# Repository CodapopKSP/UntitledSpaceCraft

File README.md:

# UntitledSpaceCraft

Untitled Space Craft is a modular controller system originally developed by Codapop. For build instructions and information, check the releases for updated documentation.

## License

This project is licensed under the [GNU General Public License v3.0 (GPL-3.0)](https://www.gnu.org/licenses/gpl-3.0.html). 

### Important License Terms

While you are free to use, modify, and redistribute the files in this project under the terms of the GPL-3.0, please note the following restrictions regarding commercial use:

- **Commercial Use**: This project is open source for hobby builders and personal use. However, you **may not** sell the hardware or any products derived from this project without explicit permission from the original creator. 

- **Modification**: You are allowed to modify the files for personal or hobby projects.

- **Attribution**: If you use or adapt this project, please give appropriate credit by mentioning the original creator.

## Contributing

Contributions are welcome! If you'd like to contribute to this project, please fork the repository and submit a pull request.

## Contact

If you have any questions or need further clarification about the license or the project, feel free to contact me at untitledspacecraft.controllers@gmail.com.

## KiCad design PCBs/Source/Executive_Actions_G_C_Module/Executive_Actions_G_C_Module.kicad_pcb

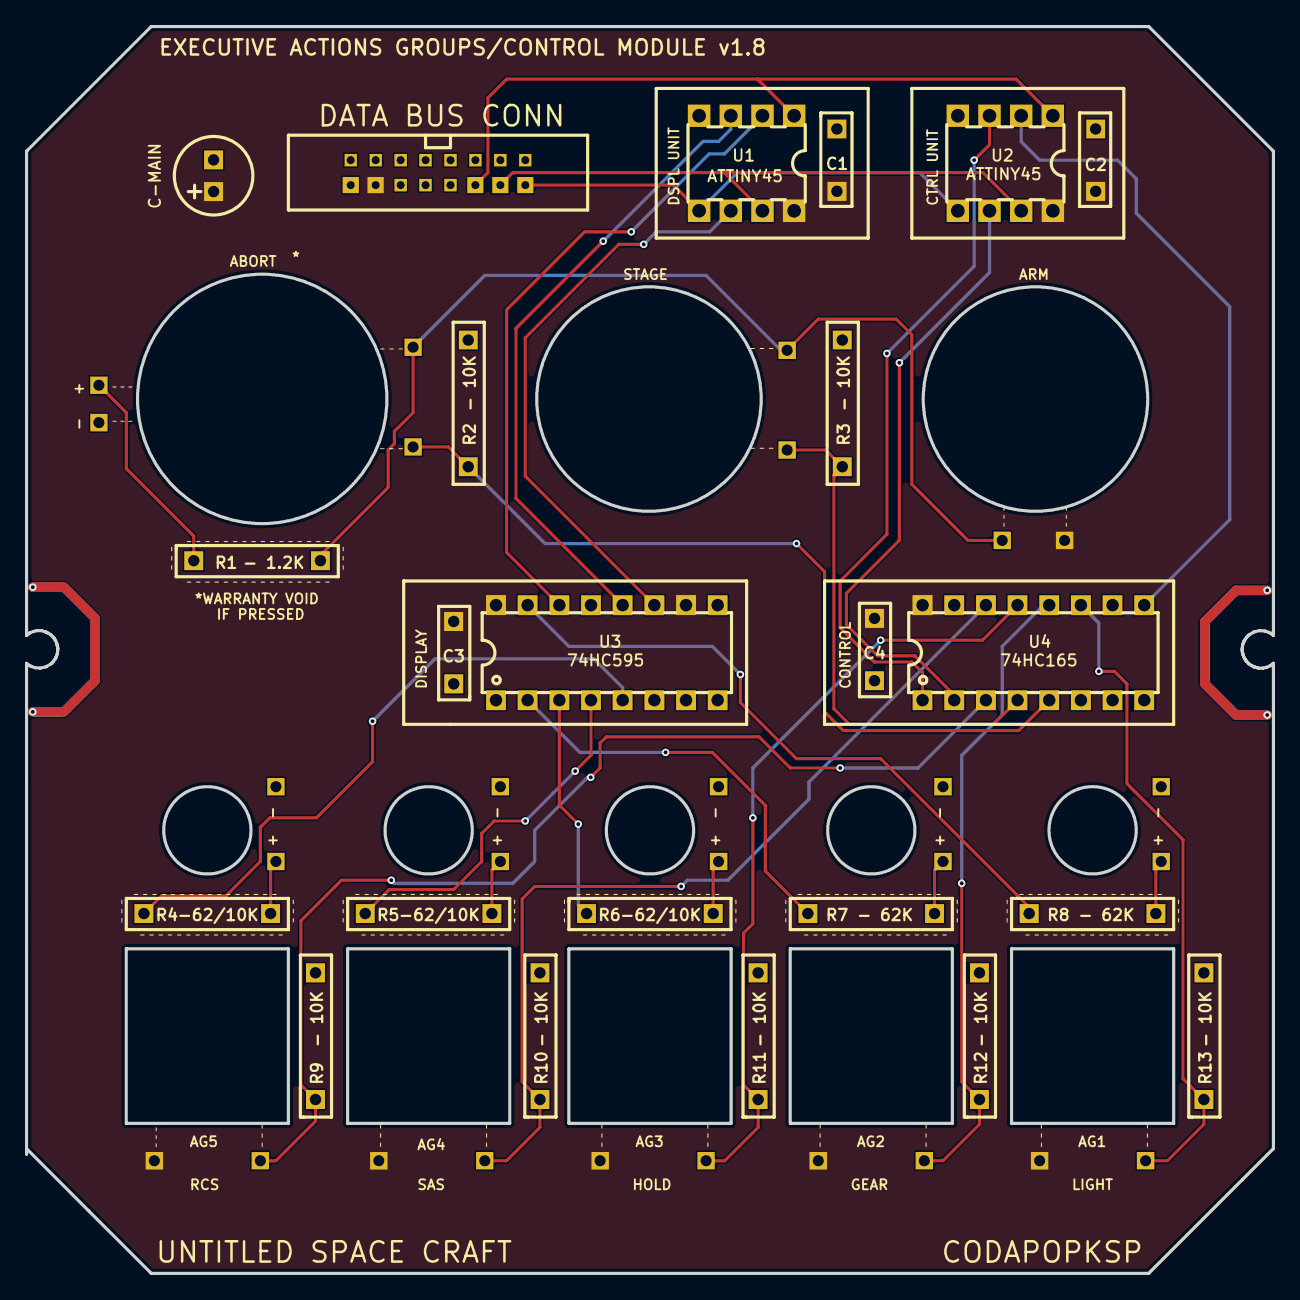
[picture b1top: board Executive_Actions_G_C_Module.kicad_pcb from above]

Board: 2 copper layers, 100.0 x 100.0 mm, 66 parts (0 on the bottom side), 30 nets.

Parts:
C1, C2, C3, C4: C104; TH_CAP_5mm
C-MAIN: 10uf; CAP-D6.3×F2.5
R1: - 1.2K; TH_RES_10mm
R2, R3, R5, R9, R10, R11, R12, R13: - 10K; TH_RES_10mm
R4: -62/10K; TH_RES_10mm
R6: - 62/10K; TH_RES_10mm
R7, R8: - 62K; TH_RES_10mm
TP_+5V: WirePad
TP_ABORT: WirePad
TP_ABORTL: WirePad
TP_ARMED: WirePad
TP_GND: WirePad
TP_STAGE: WirePad
U1, U2: ATtiny45; PDIP-8_L9.3-W6.4-P2.54-LS7.6-BL
U3: 74HC595; DIP-16_L20.0-W6.4-P2.54-LS7.6-BL
U4: 74HC165; DIP-16_L20.0-W6.4-P2.54-LS7.6-BL
WP1, WP2, WP3, WP4, WP5, WP6, WP7, WP8, WP9, WP10, WP11, WP12, WP13, WP14, WP15, WP16, WP47, WP55, WP65, WP75, WP82, WP83, WP84, WP85, WP86, WP87, WP88, WP89, WP90, WP91, WP92, WP93, WP94, WP95, WP96, WP97, WP98, WP99: WPAD-1-30AWG; WPAD-1-PTH-30AWG

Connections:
+5V: C1.2, C2.2, C3.2, C4.2, C-MAIN.1, TP_+5V.1, U1.8, U2.8, U3.10, U3.16, U4.16, WP7.1, WP75.1, WP92.1, WP94.1, WP96.1, WP98.1
ABORT: R2.1, TP_ABORT.1, U4.5
ABORTL: R1.1, TP_ABORTL.1
ARMED: R1.2, TP_ARMED.1, WP82.1, WP83.1
BUTTON1: R13.1, U4.11, WP99.1
BUTTON2: R12.1, U4.12, WP97.1
BUTTON3: R11.1, U4.13, WP95.1
BUTTON4: R10.1, U4.14, WP93.1
BUTTON5: R9.1, U4.3, WP65.1
CLOCK(Y): U2.6, U4.2
CLOCK(Y)2: U1.6, U3.11
DATA(P): U2.2, U4.9
DATA(P)2: U1.2, U3.14
GND: C1.1, C2.1, C3.1, C4.1, C-MAIN.2, R2.2, R3.2, R9.2, R10.2, R11.2, R12.2, R13.2, TP_GND.1, U1.4, U2.4, U3.8, U3.13, U4.6, U4.8, U4.15, WP8.1, WP55.1, WP84.1, WP86.1, WP89.1, WP91.1
LATCH(G): U2.3, U4.1
LATCH(G)2: U1.3, U3.12
LIGHT1: R8.1, U3.15
LIGHT2: R7.1, U3.2
LIGHT3: R6.1, U3.3
LIGHT4: R5.1, U3.4
LIGHT5: R4.1, U3.5
RESET: U1.1, U2.1, WP3.1
SCL: U1.7, U2.7, WP2.1
SDA: U1.5, U2.5, WP1.1
STAGE: R3.1, TP_STAGE.1, U4.4
WP47_1: R8.2, WP87.1
WP47_2: R7.2, WP88.1
WP47_3: R6.2, WP90.1
WP47_4: R5.2, WP85.1
WP47_5: R4.2, WP47.1

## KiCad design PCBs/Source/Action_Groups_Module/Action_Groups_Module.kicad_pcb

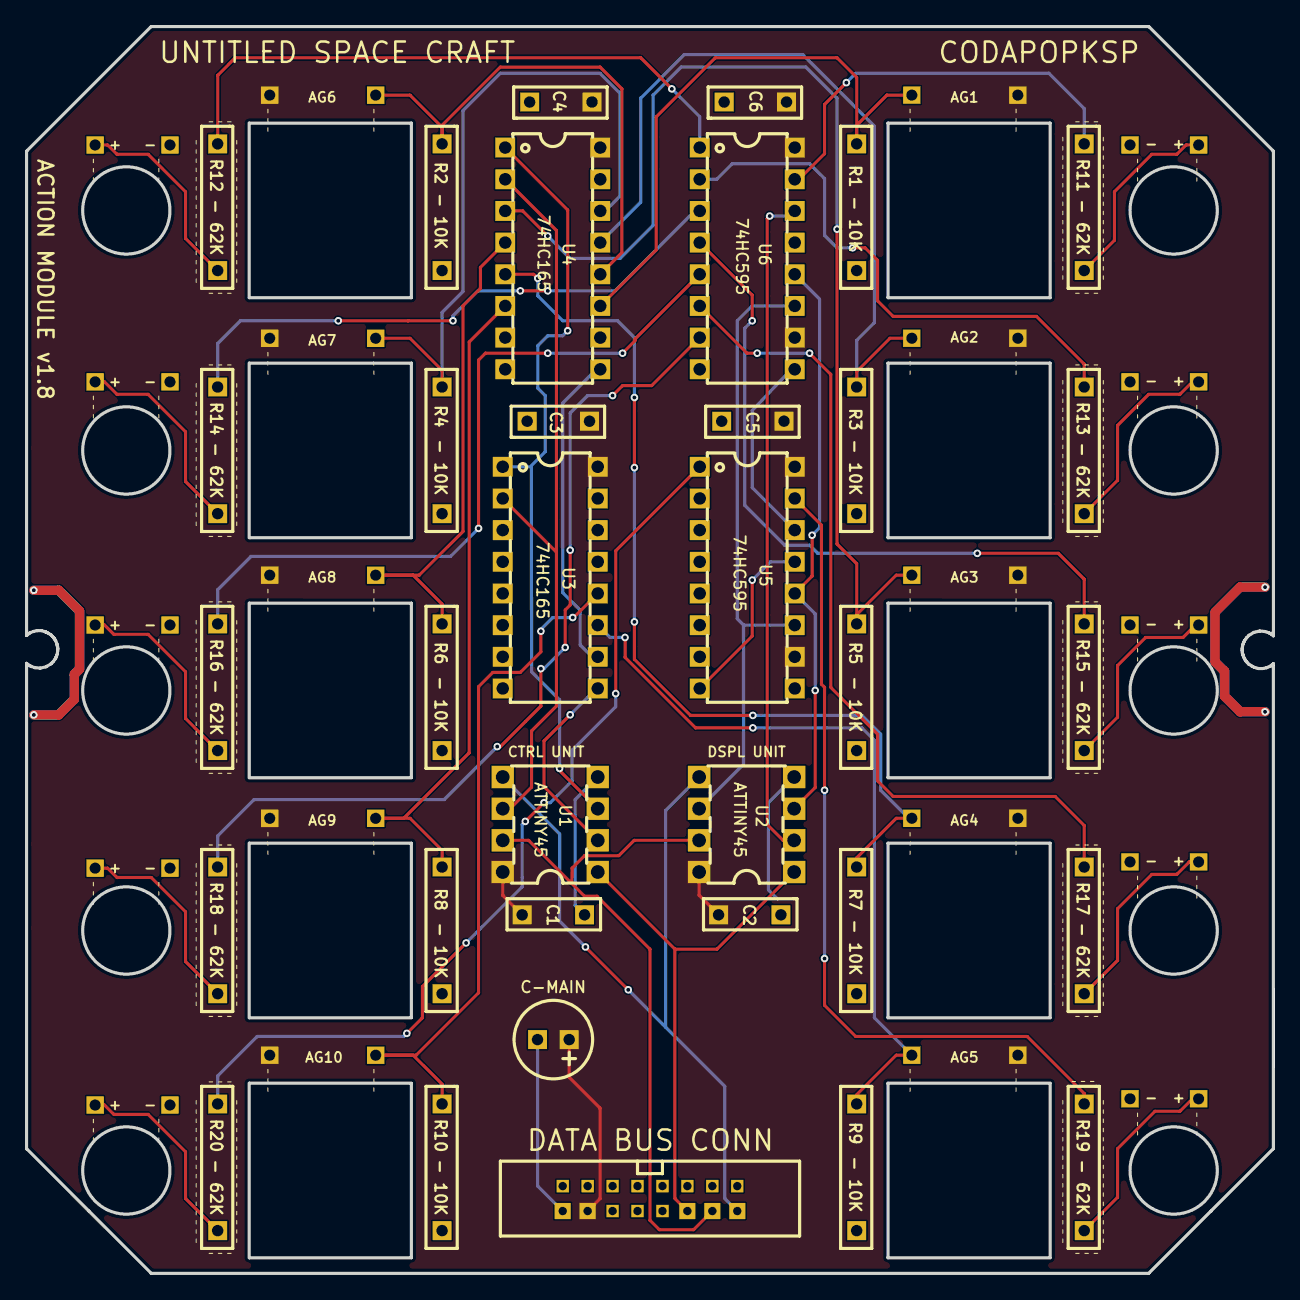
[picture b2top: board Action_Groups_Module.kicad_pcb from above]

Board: 2 copper layers, 100.0 x 100.0 mm, 89 parts (0 on the bottom side), 43 nets.

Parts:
C1, C2, C3, C4, C5, C6: C104; TH_CAP_5mm
C-MAIN: 10uf; CAP-D6.3×F2.5
R1, R2, R3, R4, R5, R6, R7, R8, R9, R10: - 10K; TH_RES_10mm
R11, R12, R13, R14, R15, R16, R17, R18, R19, R20: - 62K; TH_RES_10mm
U1, U2: ATtiny45; PDIP-8_L9.3-W6.4-P2.54-LS7.6-BL
U3, U4: 74HC165; DIP-16_L20.0-W6.4-P2.54-LS7.6-BL
U5, U6: 74HC595; DIP-16_L20.0-W6.4-P2.54-LS7.6-BL
WP41, WP42, WP43, WP44, WP45, WP46, WP47, WP48, WP49, WP50, WP51, WP52, WP53, WP54, WP55, WP56, WP57, WP58, WP59, WP60, WP61, WP62, WP63, WP64, WP65, WP66, WP67, WP68, WP69, WP70, WP71, WP72, WP73, WP74, WP75, WP76, WP77, WP78, WP83, WP84, WP85, WP86, WP87, WP88, WP89, WP90, WP91, WP92, WP93, WP94, WP95, WP96, WP97, WP98, WP99, WP100: WPAD-1-30AWG; WPAD-1-PTH-30AWG

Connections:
+5V: C1.2, C2.2, C3.2, C4.2, C5.2, C6.2, C-MAIN.1, U1.8, U2.8, U3.16, U4.16, U5.10, U5.16, U6.10, U6.16, WP71.1, WP72.1, WP73.1, WP74.1, WP75.1, WP76.1, WP77.1, WP78.1, WP83.1, WP84.1, WP92.1
CLOCK(Y): U1.6, U3.2, U4.2
CLOCK(Y)2: U2.6, U5.11, U6.11
DATA(B): U3.10, U4.9
DATA(B)2: U5.14, U6.9
DATA(P): U1.2, U3.9
DATA(P)2: U2.2, U6.14
GND: C1.1, C2.1, C3.1, C4.1, C5.1, C6.1, C-MAIN.2, R1.2, R2.2, R3.2, R4.2, R5.2, R6.2, R7.2, R8.2, R9.2, R10.2, U1.4, U2.4, U3.3, U3.4, U3.5, U3.6, U3.8, U3.13, U3.14, U3.15, U4.8, U4.15, U5.8, U5.13, U6.8, U6.13, WP49.1, WP50.1, WP51.1, WP52.1, WP53.1, WP54.1, WP55.1, WP56.1, WP57.1, WP59.1, WP91.1
LATCH(G): U1.3, U3.1, U4.1
LATCH(G)2: U2.3, U5.12, U6.12
LIGHT1: R11.1, U6.15
LIGHT2: R12.1, U6.1
LIGHT3: R13.1, U6.2
LIGHT4: R14.1, U6.3
LIGHT5: R15.1, U6.4
LIGHT6: R16.1, U6.5
LIGHT7: R17.1, U6.6
LIGHT8: R18.1, U6.7
LIGHT9: R19.1, U5.15
LIGHT10: R20.1, U5.1
RESET: U1.1, U2.1, WP96.1
SAS1: R1.1, U4.11, WP61.1
SAS2: R2.1, U4.12, WP62.1
SAS3: R3.1, U4.13, WP63.1
SAS4: R4.1, U4.14, WP64.1
SAS5: R5.1, U4.3, WP65.1
SAS6: R6.1, U4.4, WP66.1
SAS7: R7.1, U4.5, WP67.1
SAS8: R8.1, U4.6, WP68.1
SAS9: R9.1, U3.11, WP69.1
SAS10: R10.1, U3.12, WP70.1
SCL: U1.7, U2.7, WP97.1
SDA: U1.5, U2.5, WP98.1
WP41_1: R18.2, WP41.1
WP42_1: R17.2, WP42.1
WP43_1: R16.2, WP43.1
WP44_1: R15.2, WP44.1
WP45_1: R14.2, WP45.1
WP46_1: R13.2, WP46.1
WP47_1: R12.2, WP47.1
WP48_1: R11.2, WP48.1
WP58_1: R19.2, WP58.1
WP60_1: R20.2, WP60.1

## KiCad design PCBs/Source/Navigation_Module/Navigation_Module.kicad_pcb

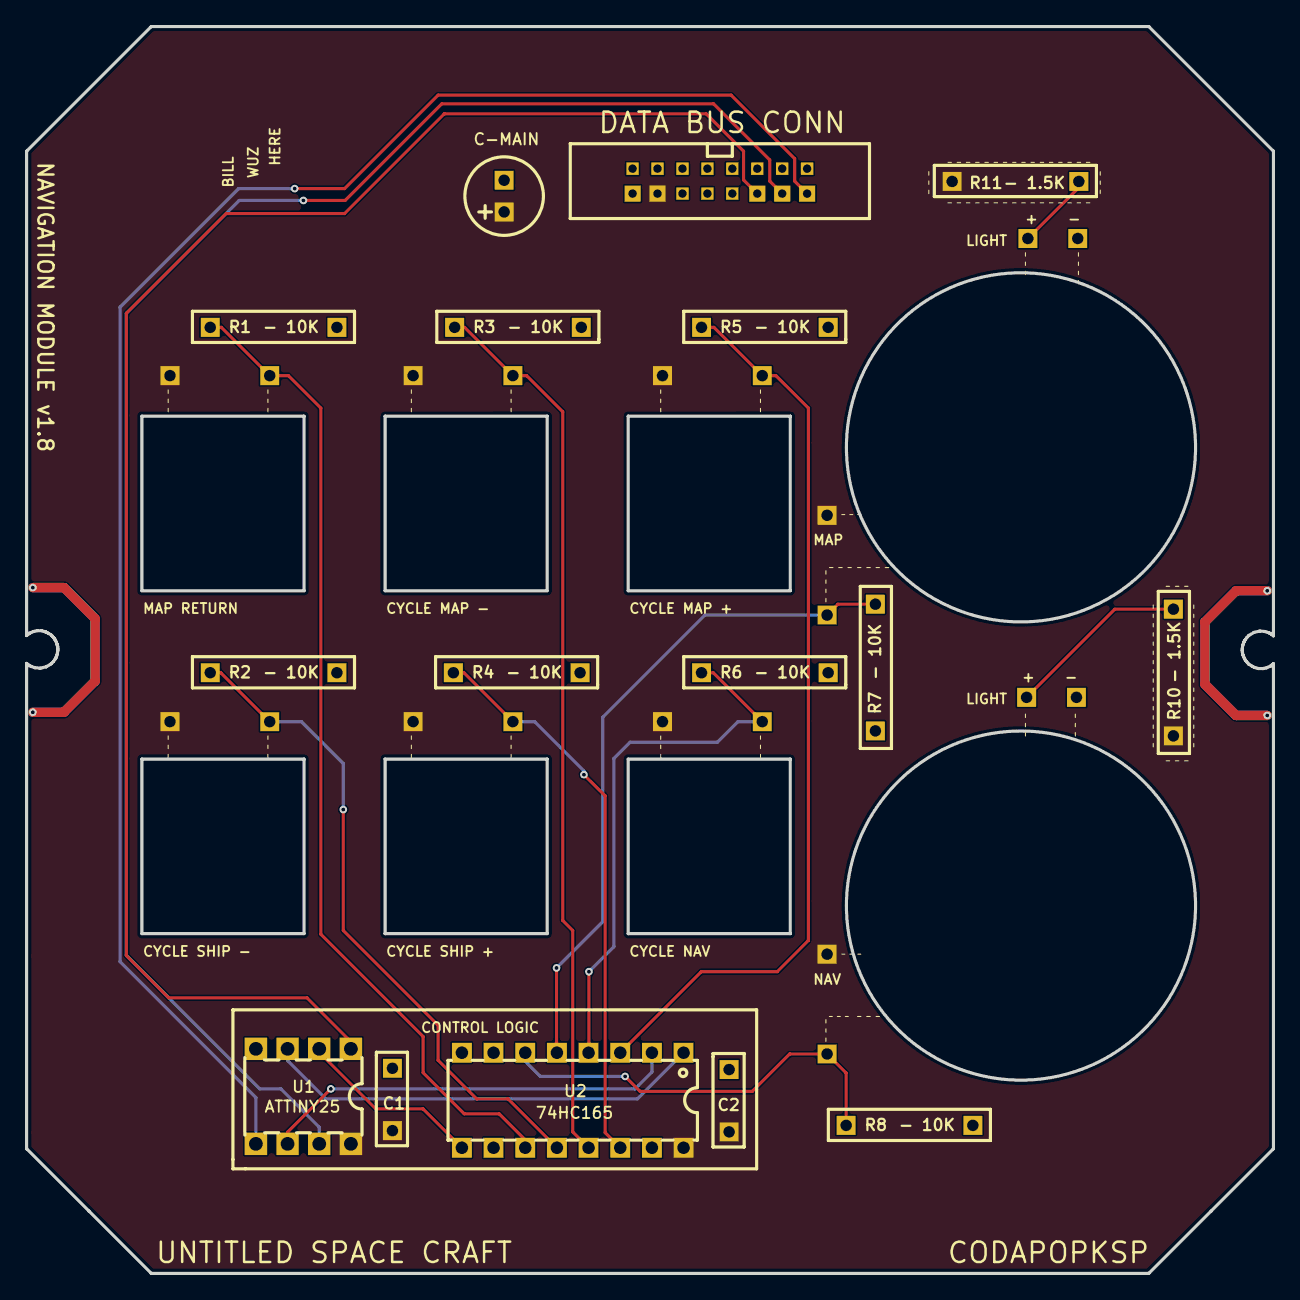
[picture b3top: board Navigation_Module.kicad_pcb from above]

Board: 2 copper layers, 100.0 x 100.0 mm, 51 parts (0 on the bottom side), 16 nets.

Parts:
C1, C2: C104; TH_CAP_5mm
C-MAIN: 10uf; CAP-D6.3×F2.5
R1, R2, R3, R4, R5, R6, R7, R8: - 10K; TH_RES_10mm
R10, R11: - 1.5K; TH_RES_10mm
TP_+5V, TP_+5V#2, TP_+5V#3, TP_+5V#4, TP_+5V#5, TP_+5V#6, TP_+5V#7, TP_+5V#8: WirePad
TP_GND: WirePad
TP_GND#2: WirePad
TP_LIGHT1, TP_LIGHT2: WirePad
TP_N1, TP_N2, TP_N3, TP_N4, TP_N5, TP_N6, TP_N7, TP_N8: WirePad
U1: ATtiny25; PDIP-8_L9.3-W6.4-P2.54-LS7.6-BL
U2: 74HC165; DIP-16_L20.0-W6.4-P2.54-LS7.6-BL
WP17, WP18, WP19, WP20, WP21, WP22, WP23, WP24, WP25, WP26, WP27, WP28, WP29, WP30, WP31, WP32: WPAD-1-30AWG; WPAD-1-PTH-30AWG

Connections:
+5V: C1.2, C2.2, C-MAIN.1, R10.1, R11.2, U1.8, U2.16, WP25.1
CLOCK(Y): U1.6, U2.2
DATA(P): U1.2, U2.9
GND: C1.1, C2.1, C-MAIN.2, R1.1, R2.1, R3.1, R4.1, R5.1, R6.1, R7.1, R8.1, U1.4, U2.8, U2.15, WP26.1
LATCH(G): U1.3, U2.1
N1: R1.2, U2.11
N2: R2.2, U2.12
N3: R3.2, U2.13
N4: R4.2, U2.14
N5: R5.2, U2.3
N6: R6.2, U2.4
N7: R7.2, U2.5
N8: R8.2, U2.6
RESET: U1.1, WP21.1
SCL: U1.7, WP20.1
SDA: U1.5, WP19.1

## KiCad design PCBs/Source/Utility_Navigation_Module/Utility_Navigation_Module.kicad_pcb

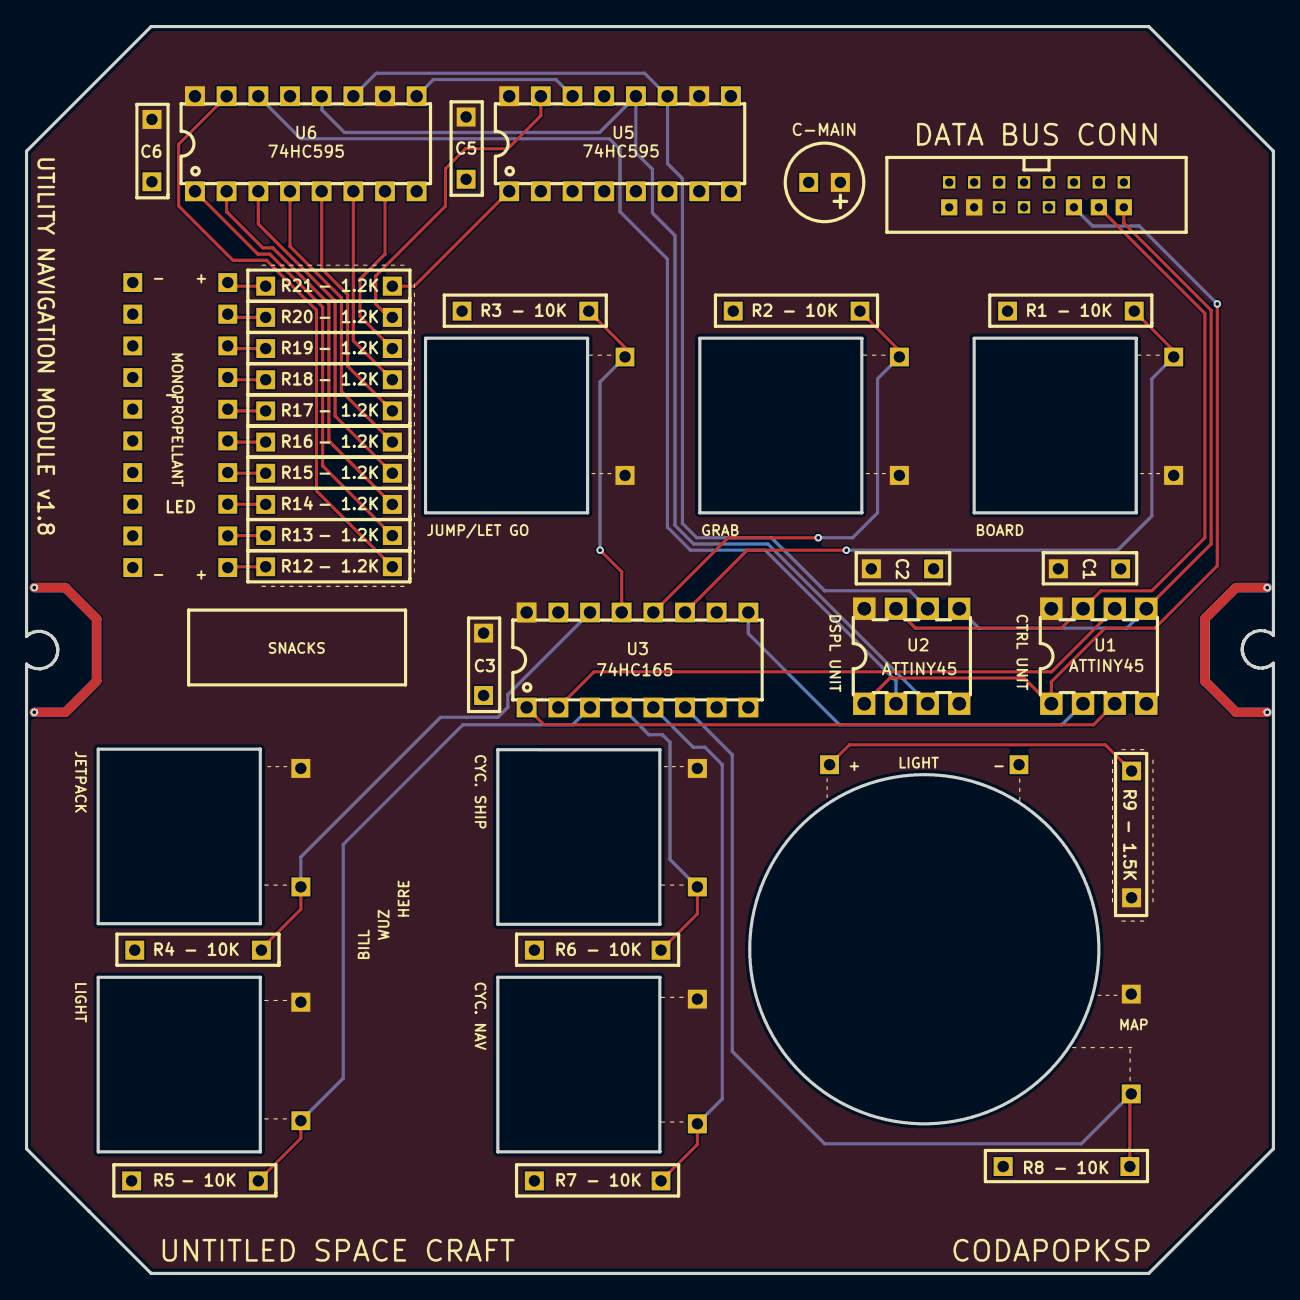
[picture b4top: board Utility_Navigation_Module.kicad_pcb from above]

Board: 2 copper layers, 100.0 x 100.0 mm, 65 parts (0 on the bottom side), 40 nets.

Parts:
C1, C2, C3, C5, C6: C104; TH_CAP_5mm
C-MAIN: 10uf; CAP-D6.3×F2.5
LED: _
R1, R2, R3, R4, R5, R6, R7, R8: - 10K; TH_RES_10mm
R9: - 1.5K; TH_RES_10mm
R12, R13, R14, R15, R16, R17, R18, R19, R20, R21: - 1.2K; TH_RES_10mm
TP_+5V, TP_+5V#2, TP_+5V#3, TP_+5V#4, TP_+5V#5, TP_+5V#6, TP_+5V#7, TP_+5V#8: WirePad
TP_EVA1, TP_EVA2, TP_EVA3, TP_EVA4, TP_EVA5: WirePad
TP_GND: WirePad
TP_LIGHT0: WirePad
TP_N1, TP_N2, TP_N3: WirePad
U1, U2: ATtiny45; PDIP-8_L9.3-W6.4-P2.54-LS7.6-BL
U3: 74HC165; DIP-16_L20.0-W6.4-P2.54-LS7.6-BL
U5, U6: 74HC595; DIP-16_L20.0-W6.4-P2.54-LS7.6-BL
WP1, WP2, WP3, WP4, WP5, WP6, WP7, WP8, WP9, WP10, WP11, WP12, WP13, WP14, WP15, WP16: WPAD-1-30AWG; WPAD-1-PTH-30AWG

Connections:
+5V: C1.2, C2.2, C3.2, C5.2, C6.2, C-MAIN.1, R9.2, TP_+5V.8, TP_+5V#4.8, TP_+5V#6.9, TP_+5V#8.15, U1.8, U2.8, U3.16, U5.10, U5.16, U6.10, U6.16, WP7.1
CLOCK(Y): U1.6, U3.2
CLOCK(Y)2: U2.6, U5.11, U6.11
DATA(B)2: U5.14, U6.9
DATA(P): U1.2, U3.9
DATA(P)2: U2.2, U6.14
EVA1: R1.1, TP_EVA1.20, U3.11
EVA2: R2.1, TP_EVA2.18, U3.12
EVA3: R3.1, TP_EVA3.16, U3.13
EVA4: R4.1, TP_EVA4.1, U3.14
EVA5: R5.1, TP_EVA5.1, U3.3
GND: C1.1, C2.1, C3.1, C5.1, C6.1, C-MAIN.2, LED.GND, R1.2, R2.2, R3.2, R4.2, R5.2, R6.2, R7.2, R8.2, U1.4, U2.4, U3.8, U3.15, U5.8, U5.13, U6.8, U6.13, WP8.1
LATCH(G): U1.3, U3.1
LATCH(G)2: U2.3, U5.12, U6.12
LIGHT1: R12.1, U6.15
LIGHT2: R13.1, U6.1
LIGHT3: R14.1, U6.2
LIGHT4: R15.1, U6.3
LIGHT5: R16.1, U6.4
LIGHT6: R17.1, U6.5
LIGHT7: R18.1, U6.6
LIGHT8: R19.1, U6.7
LIGHT9: R20.1, U5.15
LIGHT10: R21.1, U5.1
N1: R6.1, TP_N1.2, U3.4
N2: R7.1, U3.5
N3: R8.1, U3.6
RESET: U1.1, U2.1, WP3.1
SCL: U1.7, U2.7, WP2.1
SDA: U1.5, U2.5, WP1.1
WP41_1: LED.GND, R19.2
WP42_1: LED.GND, R18.2
WP43_1: LED.GND, R17.2
WP44_1: LED.GND, R16.2
WP45_1: LED.GND, R15.2
WP46_1: LED.GND, R14.2
WP47_1: LED.GND, R13.2
WP48_1: LED.GND, R12.2
WP58_1: LED.GND, R20.2
WP60_1: LED.GND, R21.2

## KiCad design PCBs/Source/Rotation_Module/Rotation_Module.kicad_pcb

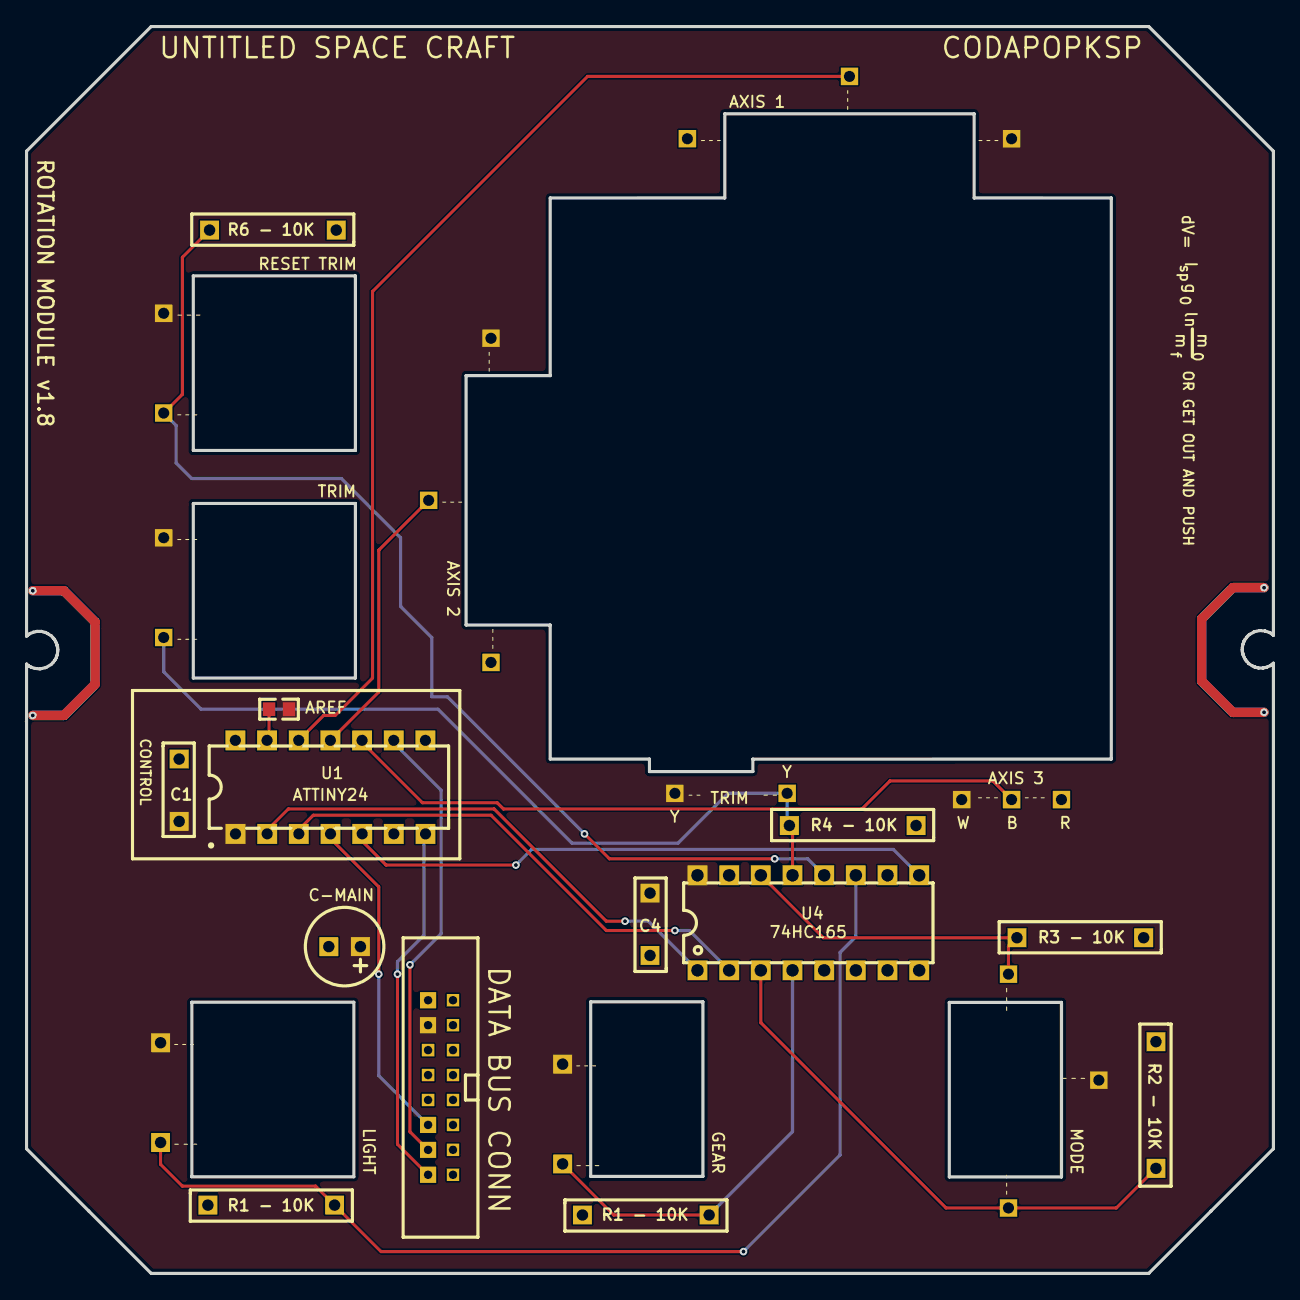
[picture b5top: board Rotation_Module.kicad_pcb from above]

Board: 2 copper layers, 100.0 x 100.0 mm, 63 parts (0 on the bottom side), 18 nets.

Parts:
AREF: 10k; R0603
C1, C4: C104; TH_CAP_5mm
C-MAIN: 10uf; CAP-D6.3×F2.5
R1, R1#2, R2, R3, R4, R6: - 10K; TH_RES_10mm
TP_+5V, TP_+5V#2, TP_+5V#3, TP_+5V#4, TP_+5V#5, TP_+5V#6, TP_+5V#7, TP_+5V#8, TP_+5V#9, TP_+5V#10: WirePad
TP_AREF: WirePad
TP_AXIS1, TP_AXIS1#2, TP_AXIS2, TP_AXIS2#2, TP_AXIS3, TP_AXIS3#2: WirePad
TP_CLOCK_Y_: WirePad
TP_CRUISE: WirePad
TP_DATA_P_: WirePad
TP_GEAR: WirePad
TP_GND: WirePad
TP_GND#2, TP_GND#3, TP_GND#4: WirePad
TP_LATCH_G_: WirePad
TP_LIGHTS: WirePad
TP_MODE1, TP_MODE2: WirePad
TP_Pad_gge45412: WirePad
TP_RESET: WirePad
TP_RESETTRIM: WirePad
TP_SCL: WirePad
TP_SDA: WirePad
TP_TRIM: WirePad
TP_TRIM#2: WirePad
U4: 74HC165; DIP-16_L20.0-W6.4-P2.54-LS7.6-BL
WP11, WP24, WP25, WP38, WP39, WP43, WP44, WP45, WP46, WP47, WP48, WP49, WP50, WP51, WP52, WP53: WPAD-1-30AWG; WPAD-1-PTH-30AWG

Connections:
+5V: AREF.2, C1.2, C4.2, C-MAIN.1, TP_+5V.1, TP_+5V#2.1, TP_+5V#3.1, TP_+5V#4.1, TP_+5V#5.1, TP_+5V#6.1, TP_+5V#7.1, TP_+5V#8.1, TP_+5V#9.1, TP_+5V#10.1, U4.16, WP46.1
AREF: AREF.1, TP_AREF.13
AXIS1: TP_AXIS1.12, TP_AXIS1#2.1
AXIS2: TP_AXIS2.11, TP_AXIS2#2.1
AXIS3: TP_AXIS3.10, TP_AXIS3#2.1
CLOCK(Y): TP_CLOCK_Y_.3, U4.2
DATA(P): TP_DATA_P_.5, U4.9
GEAR: R1#2.2, TP_GEAR.1, U4.4
GND: C1.1, C4.1, C-MAIN.2, R1.1, R1#2.1, R2.1, R3.1, R4.1, R6.1, TP_GND.1, TP_GND#2.1, TP_GND#3.14, TP_GND#4.1, U4.5, U4.6, U4.8, U4.15, WP45.1
LATCH(G): TP_LATCH_G_.2, U4.1
LIGHTS: R1.2, TP_LIGHTS.1, U4.11
MODE1: R3.2, TP_MODE1.1, U4.14
MODE2: R2.2, TP_MODE2.1, U4.3
RESET: TP_RESET.4, WP50.1
RESETTRIM: R6.2, TP_RESETTRIM.1, U4.12
SCL: TP_SCL.9, WP51.1
SDA: TP_SDA.7, WP52.1
TRIM: R4.2, TP_TRIM.1, TP_TRIM#2.1, U4.13

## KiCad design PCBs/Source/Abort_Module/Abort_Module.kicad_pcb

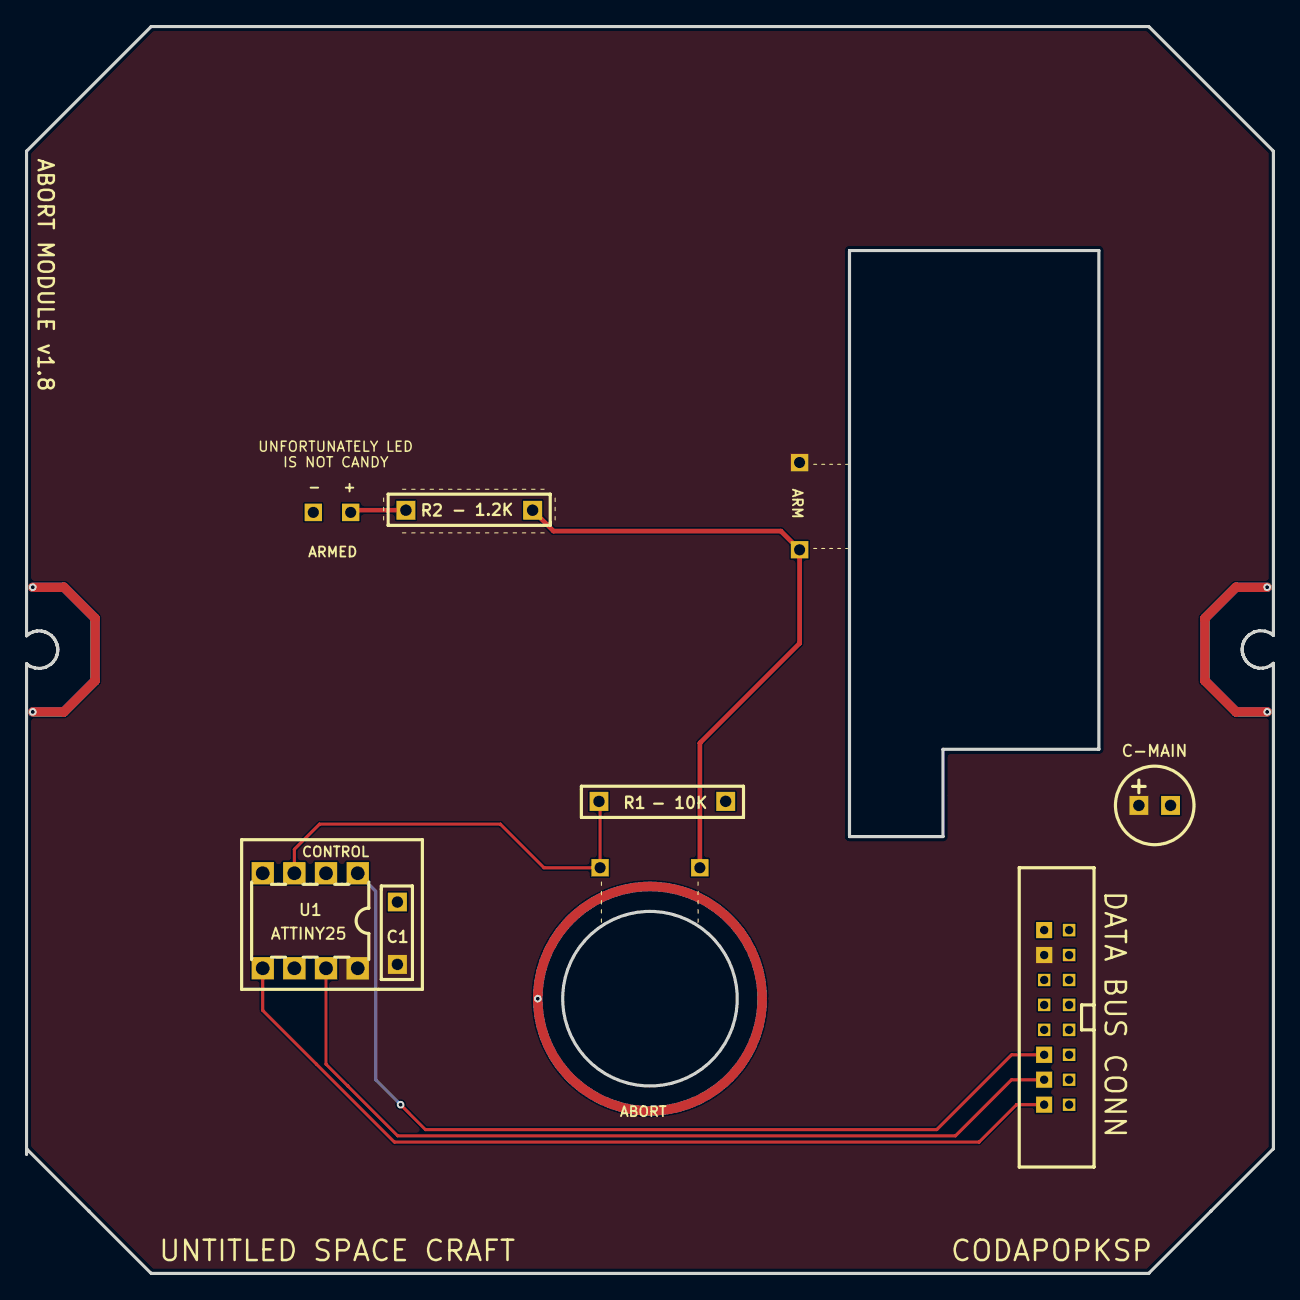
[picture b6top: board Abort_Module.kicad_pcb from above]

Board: 2 copper layers, 100.0 x 100.0 mm, 27 parts (0 on the bottom side), 8 nets.

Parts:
C1: C104; TH_CAP_5mm
C-MAIN: 1u; CAP-D6.3×F2.5
R1: - 10K; TH_RES_10mm
R2: - 1.2K; TH_RES_10mm
TP_+5V: WirePad
TP_ARMED: WirePad
TP_GND: WirePad
TP_LIGHT: WirePad
TP_STAGE: WirePad
U1: ATtiny25; PDIP-8_L9.3-W6.4-P2.54-LS7.6-BL
WP84, WP85, WP86, WP87, WP88, WP89, WP90, WP91, WP92, WP93, WP94, WP95, WP96, WP97, WP98, WP99, WP100: WPAD-1-30AWG; WPAD-1-PTH-30AWG

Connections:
+5V: C1.2, C-MAIN.1, TP_+5V.1, U1.8, WP92.1
ARMED: R2.1, TP_ARMED.1, WP100.1
GND: C1.1, C-MAIN.2, R1.2, TP_GND.1, U1.4, WP93.1
LIGHT: R2.2, TP_LIGHT.1
RESET: U1.1, WP88.1
SCL: U1.7, WP87.1
SDA: U1.5, WP86.1
STAGE: R1.1, TP_STAGE.1, U1.3

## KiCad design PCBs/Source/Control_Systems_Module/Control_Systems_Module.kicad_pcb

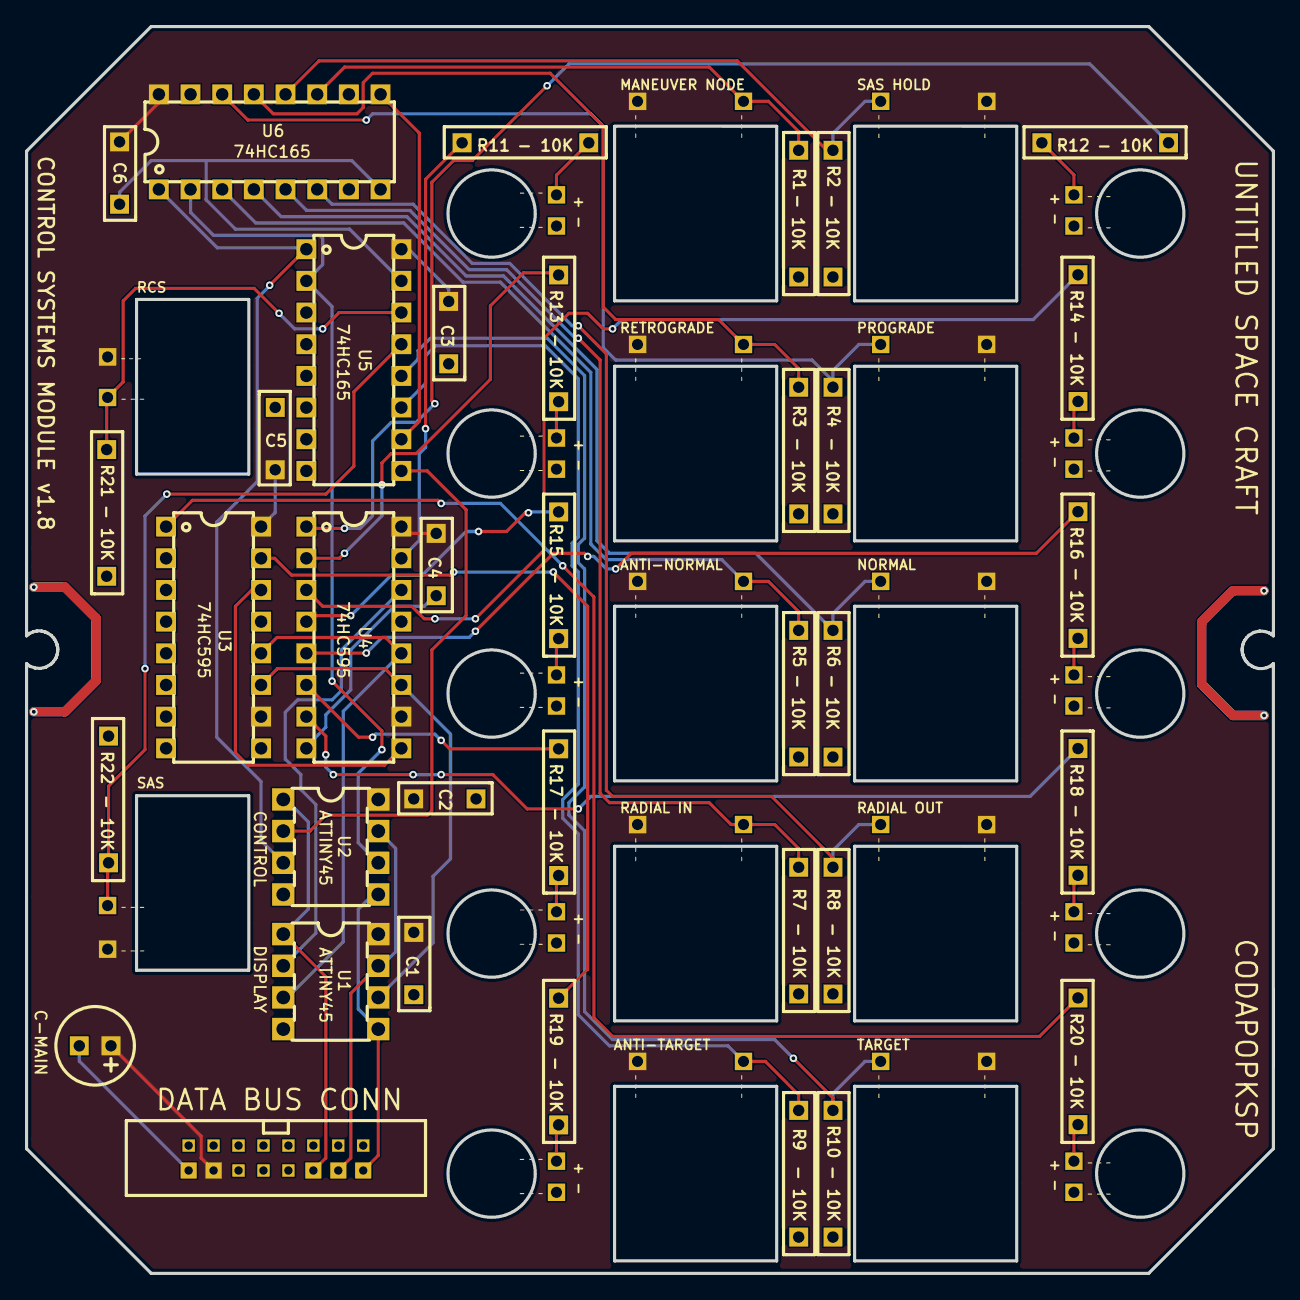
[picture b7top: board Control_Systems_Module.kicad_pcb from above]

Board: 2 copper layers, 100.0 x 100.0 mm, 95 parts (0 on the bottom side), 45 nets.

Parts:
C1, C2, C3, C4, C5, C6: C104; TH_CAP_5mm
C-MAIN: 10uf; CAP-D6.3×F2.5
R1, R2, R3, R4, R5, R6, R7, R8, R9, R10, R11, R12, R13, R14, R15, R16, R17, R18, R19, R20, R21, R22: - 10K; TH_RES_10mm
U1, U2: ATtiny45; PDIP-8_L9.3-W6.4-P2.54-LS7.6-BL
U3, U4: 74HC595; DIP-16_L20.0-W6.4-P2.54-LS7.6-BL
U5, U6: 74HC165; DIP-16_L20.0-W6.4-P2.54-LS7.6-BL
WP1, WP2, WP3, WP4, WP5, WP6, WP7, WP8, WP9, WP10, WP11, WP12, WP13, WP14, WP15, WP16, WP41, WP42, WP43, WP44, WP45, WP46, WP47, WP48, WP49, WP50, WP51, WP52, WP53, WP54, WP55, WP56, WP57, WP58, WP59, WP60, WP61, WP62, WP63, WP64, WP65, WP66, WP67, WP68, WP69, WP70, WP71, WP72, WP73, WP74, WP75, WP76, WP77, WP78, WP79, WP80, WP81, WP82, WP83, WP84: WPAD-1-30AWG; WPAD-1-PTH-30AWG

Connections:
+5V: C1.2, C2.2, C3.2, C4.2, C5.2, C6.2, C-MAIN.1, U1.8, U2.8, U3.10, U3.16, U4.10, U4.16, U5.16, U6.16, WP7.1, WP71.1, WP72.1, WP73.1, WP74.1, WP75.1, WP76.1, WP77.1, WP78.1, WP81.1, WP82.1, WP83.1, WP84.1
CLOCK(Y): U2.6, U5.2, U6.2
CLOCK(Y)2: U1.6, U3.11, U4.11
DATA(B): U5.10, U6.9
DATA(B)2: U3.14, U4.9
DATA(P): U2.2, U5.9
DATA(P)2: U1.2, U4.14
GND: C1.1, C2.1, C3.1, C4.1, C5.1, C6.1, C-MAIN.2, R1.1, R2.1, R3.1, R4.1, R5.1, R6.1, R7.1, R8.1, R9.1, R10.1, R21.1, R22.1, U1.4, U2.4, U3.8, U3.13, U4.8, U4.13, U5.3, U5.4, U5.5, U5.6, U5.8, U5.15, U6.8, U6.15, WP8.1, WP49.1, WP50.1, WP51.1, WP52.1, WP53.1, WP54.1, WP55.1, WP56.1, WP57.1, WP59.1
LATCH(G): U2.3, U5.1, U6.1
LATCH(G)2: U1.3, U3.12, U4.12
LIGHT1: R11.2, U4.15
LIGHT2: R12.1, U4.1
LIGHT3: R13.2, U4.2
LIGHT4: R14.1, U4.3
LIGHT5: R15.2, U4.4
LIGHT6: R16.1, U4.5
LIGHT7: R17.2, U4.6
LIGHT8: R18.1, U4.7
LIGHT9: R19.2, U3.15
LIGHT10: R20.1, U3.1
RCS: R21.2, U5.14, WP80.1
RESET: U1.1, U2.1, WP3.1
SAS: R22.2, U5.13, WP79.1
SAS1: R1.2, U6.11, WP61.1
SAS2: R2.2, U6.12, WP62.1
SAS3: R3.2, U6.13, WP63.1
SAS4: R4.2, U6.14, WP64.1
SAS5: R5.2, U6.3, WP65.1
SAS6: R6.2, U6.4, WP66.1
SAS7: R7.2, U6.5, WP67.1
SAS8: R8.2, U6.6, WP68.1
SAS9: R9.2, U5.11, WP69.1
SAS10: R10.2, U5.12, WP70.1
SCL: U1.7, U2.7, WP2.1
SDA: U1.5, U2.5, WP1.1
WP41_1: R18.2, WP41.1
WP42_1: R17.1, WP42.1
WP43_1: R16.2, WP43.1
WP44_1: R15.1, WP44.1
WP45_1: R14.2, WP45.1
WP46_1: R13.1, WP46.1
WP47_1: R12.2, WP47.1
WP48_1: R11.1, WP48.1
WP58_1: R19.1, WP58.1
WP60_1: R20.2, WP60.1

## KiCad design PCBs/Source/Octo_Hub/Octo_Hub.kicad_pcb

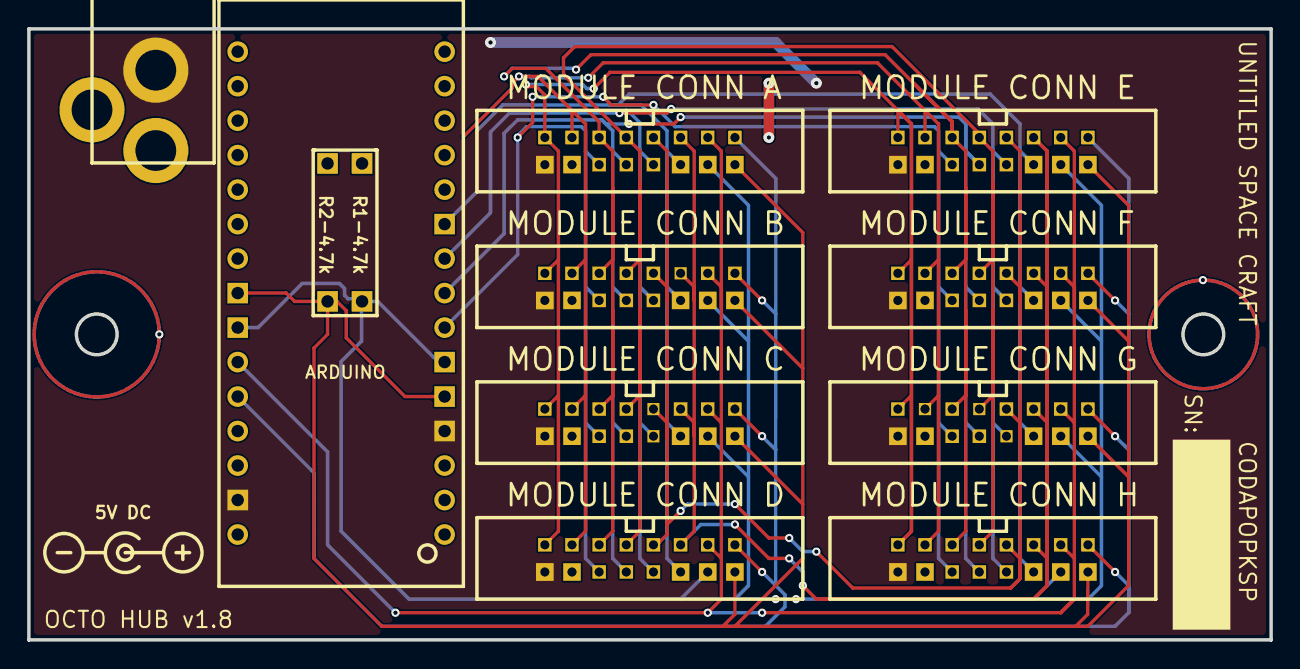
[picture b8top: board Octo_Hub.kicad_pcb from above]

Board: 2 copper layers, 91.5 x 45.0 mm, 132 parts (0 on the bottom side), 16 nets.

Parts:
ARDUINO: Arduino_Nano_Header; DIP-30_L43.18-W15.24-ARDUINONANO
NONE: _
NONEAWD: _
U1: PJ-102A
WP17, WP18, WP19, WP20, WP21, WP22, WP23, WP24, WP25, WP26, WP27, WP28, WP29, WP30, WP31, WP32, WP33, WP34, WP35, WP36, WP37, WP38, WP39, WP40, WP41, WP42, WP43, WP44, WP45, WP46, WP47, WP48, WP49, WP50, WP51, WP52, WP53, WP54, WP55, WP56, WP57, WP58, WP59, WP60, WP61, WP62, WP63, WP64, WP65, WP66, WP67, WP68, WP69, WP70, WP71, WP72, WP73, WP74, WP75, WP76, WP77, WP78, WP79, WP80, WP81, WP82, WP83, WP84, WP85, WP86, WP87, WP88, WP89, WP90, WP91, WP92, WP93, WP94, WP95, WP96, WP97, WP98, WP99, WP100, WP101, WP102, WP103, WP104, WP105, WP106, WP107, WP108, WP109, WP110, WP111, WP112, WP113, WP114, WP115, WP116, WP117, WP118, WP119, WP120, WP121, WP122, WP123, WP124, WP125, WP126, WP127, WP128, WP129, WP130, WP131, WP132, WP133, WP134, WP135, WP136, WP137, WP138, WP139, WP140, WP141, WP142, WP143, WP144: WPAD-1-30AWG; WPAD-1-PTH-30AWG

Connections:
+5V: NONE.2, NONE.4, U1.TIP, WP24.1, WP41.1, WP57.1, WP73.1, WP89.1, WP104.1, WP120.1, WP136.1
ANALOG0: WP20.1, WP45.1, WP61.1, WP77.1, WP93.1, WP100.1, WP116.1, WP132.1
ANALOG1: WP19.1, WP46.1, WP62.1, WP78.1, WP94.1, WP99.1, WP115.1, WP131.1
ANALOG2: WP18.1, WP47.1, WP63.1, WP79.1, WP95.1, WP98.1, WP114.1, WP130.1
ANALOG3: WP32.1, WP33.1, WP49.1, WP65.1, WP81.1, WP112.1, WP128.1, WP144.1
ANALOG4: ARDUINO.25, WP31.1, WP34.1, WP50.1, WP66.1, WP82.1, WP111.1, WP127.1, WP143.1
ANALOG5: ARDUINO.26, WP17.1, WP48.1, WP64.1, WP80.1, WP96.1, WP97.1, WP113.1, WP129.1
DIGITAL0: WP22.1, WP43.1, WP59.1, WP75.1, WP91.1, WP102.1, WP118.1, WP134.1
DIGITAL1: WP21.1, WP44.1, WP60.1, WP76.1, WP92.1, WP101.1, WP117.1, WP133.1
DIGITAL2: ARDUINO.7, WP25.1, WP40.1, WP56.1, WP72.1, WP88.1, WP105.1, WP121.1, WP137.1
DIGITAL3: ARDUINO.8, WP26.1, WP39.1, WP55.1, WP71.1, WP87.1, WP106.1, WP122.1, WP138.1
DIGITAL4: ARDUINO.9, WP27.1, WP38.1, WP54.1, WP70.1, WP86.1, WP107.1, WP123.1, WP139.1
GND: ARDUINO.4, ARDUINO.29, U1.RING, WP23.1, WP42.1, WP58.1, WP74.1, WP90.1, WP103.1, WP119.1, WP135.1
RESET: ARDUINO.10, WP28.1, WP37.1, WP53.1, WP69.1, WP85.1, WP108.1, WP124.1, WP140.1
SCL: ARDUINO.6, ARDUINO.24, NONE.5, WP29.1, WP36.1, WP52.1, WP68.1, WP84.1, WP109.1, WP125.1, WP141.1
SDA: ARDUINO.5, ARDUINO.23, NONE.3, WP30.1, WP35.1, WP51.1, WP67.1, WP83.1, WP110.1, WP126.1, WP142.1

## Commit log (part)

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2024-10-11 Update license and README.
2024-10-11 Fix README.
2024-10-11 Add USC project files.
2024-11-04 invert the RKT pitch axis
2024-11-04 calibrated throttle values
2024-11-04 raise the min throttle deadzone
2024-12-15 Increase module laser cut magnet holes slightly.
2026-02-22 Add modularized firmware. Upgrade firmware to v3.0.0
2026-05-21 Add animated SVG to README
2026-05-21 Improve controller animation
2026-06-19 Add schematics
2026-06-19 Add BoM and Utility Schematics.
2026-06-19 Update BoM
2026-06-20 Update documentation
2026-06-22 Update docs
